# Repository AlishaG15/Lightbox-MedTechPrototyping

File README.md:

# Lightbox

A custom embedded systems project built for MedTech Prototyping (BME 254) at Duke University, Spring 2026 — a 3D-printed panda enclosure housing a hand-soldered PCB, Arduino Nano Every, and three independently controlled LEDs (two eyes and a nose).

---

## Overview

When a button is pressed, the panda's eyes light up for 5 seconds and its nose blinks for 10 seconds. The brightness of the eyes and blink rate of the nose are each controlled by a dedicated potentiometer mounted in the ears. An onboard heartbeat LED blinks at 1 Hz in all states to confirm the device is running.

---

## Hardware

| Component | Detail |
|---|---|
| Microcontroller | Arduino Nano Every (ATmega4809) |
| PCB | Custom single-sided board, hand-milled and soldered |
| LED drivers | IRFZ44 N-channel MOSFETs |
| Enclosure | 3D-printed PLA, two-part snap fit |
| Power | 9 V battery with SPST toggle switch |
| Controls | SPST push button + 2× 10 kΩ potentiometers |

---

## Firmware

Written in C++ using the Arduino framework via PlatformIO. Key design decisions:

- **State machine** with three explicit states: `IDLE`, `ANALOG_READ`, and `LED_OUTPUT`
- **Interrupt-driven** button input using `attachInterrupt()` — no polling in the main loop
- **Non-blocking timing** throughout using `millis()` — no `delay()` calls anywhere
- **PWM brightness control** on the eye LEDs via `analogWrite()`, mapped linearly from the potentiometer ADC reading
- **Clean digital blink** on the nose LED using `digitalWrite()` to avoid the Nano Every's 255/256 PWM artifact
- All pin assignments and timing constants defined as `#define` macros at the top of the file

```
IDLE ──(button press)──▶ ANALOG_READ ──▶ LED_OUTPUT ──(10 s elapsed)──▶ IDLE
```

---

## Testing Results

All measurements taken with a Tektronix TBS 1102B oscilloscope. Full analysis, with regression fits and 95% confidence intervals, is in the [technical report](testing/technical_report.ipynb) ([HTML version](testing/technical_report.html)); raw data is in [`testing/`](testing).

**Heartbeat LED**
- Period: 1000 ms, Frequency: 1.000 Hz, Duty cycle: 50.0%
- Identical in both IDLE and LED_OUTPUT states
- Zero measurable variation across 10 trials in each state (limited by oscilloscope resolution)

**Eye LED brightness (vs. potentiometer resistance)**
- Linear relationship (R² ≈ 1.0) from 0% duty cycle at max resistance to ~80% at minimum
- Did not reach 100% due to potentiometer mechanical travel limits

**Nose LED blink rate (vs. potentiometer resistance)**
- Linear relationship from 5.00 Hz (max resistance) to 7.45 Hz (min resistance)
- Lower bound matches spec exactly; upper bound limited by the same pot range constraint

---

## Gallery

| Assembled | Back panel |
|---|---|
|  |  |

| Internals (PCB) | Internals (Arduino + connectors) |
|---|---|
|  |  |

---

## Repository Layout

| Folder | Contents |
|---|---|
| [`src/`](src) | Firmware (`main.cpp`) |
| [`circuit/`](circuit) | KiCad schematic, PCB layout and MOSFET footprint |
| [`cad/`](cad) | Enclosure renders |
| [`testing/`](testing) | Oscilloscope data and technical report |
| [`images/`](images) | Photos of the assembled device |

---

## Built With

- **PlatformIO** — build system and upload toolchain
- **KiCad** — schematic capture and PCB layout
- **Fusion 360 / CAD** — enclosure design
- **Python / Jupyter** — data analysis and technical report (scipy, matplotlib, pandas)

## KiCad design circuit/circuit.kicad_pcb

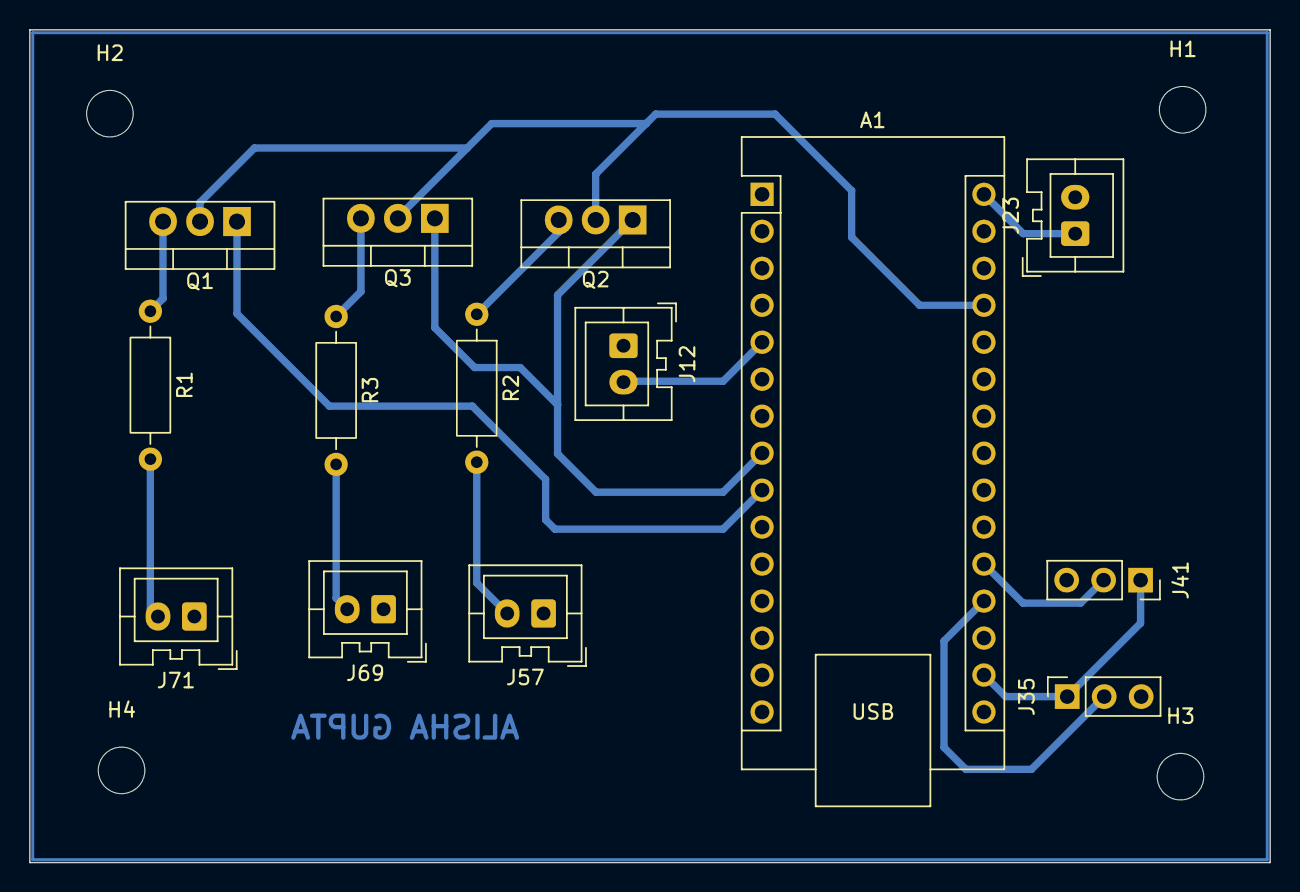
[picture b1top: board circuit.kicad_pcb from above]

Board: 2 copper layers, 85.2 x 57.2 mm, 18 parts (0 on the bottom side), 15 nets.

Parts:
A1: Arduino_Nano_Every; Arduino_Nano
H1, H2, H3, H4: MountingHole; MountingHole_3.2mm_M3
J12, J23: Conn_01x02_Pin; JST_XA_B02B-XASK-1_1x02_P2.50mm_Vertical
J35: POT_BRIGHT_CONN; PinSocket_1x03_P2.54mm_Vertical
J41: POT_BLINK_CONN; PinSocket_1x03_P2.54mm_Vertical
J57, J69, J71: B02B-XASK-1; JST_XA_B02B-XASK-1_1x02_P2.50mm_Vertical
Q1, Q2, Q3: IRFZ44N; TO-220-3_Vertical
R1, R2, R3: 1k; R_Axial_DIN0207_L6.3mm_D2.5mm_P10.16mm_Horizontal

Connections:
+3.3V: A1.17 (3V3), J35.1, J41.1
+5V: A1.27 (+5V), Q1.2, Q2.2, Q3.2
+9V: A1.30 (VIN), J23.1
BLINK_OUT: A1.9 (D6), Q1.1
BRIGHT_OUT: A1.8 (D5), Q2.1, Q3.1
BUTTON_IN: A1.5 (D2), J12.2
GND: A1.4 (GND), A1.29 (GND), J12.1, J23.2, J35.3, J41.3, J57.1, J69.1, J71.1
unnamed: J57.2, R2.2
unnamed: J69.2, R3.2
unnamed: J71.2, R1.2
unnamed: Q1.3, R1.1
unnamed: Q2.3, R2.1
unnamed: Q3.3, R3.1
POT_BLINK: A1.20 (A1), J41.2
POT_BRIGHT: A1.19 (A0), J35.2

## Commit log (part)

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2023-04-12 add resources
2023-04-12 Fix Nano Every chip and add Nane 33 Sense platform
2023-04-12 add button interrupt and blinking LED logic
2023-04-13 add tip about TTY permissions
2023-04-13 Add more functionality.
    * One-shot mode
    * Comments (including where timers should be used)
    * Sleep mode
2023-04-17 add comments about AVR-specific sleep library
2023-04-18 add analog voltage read hooks
2023-04-18 WIP: add KiCad ckt
2023-04-19 update schematic with components and notes
2023-04-19 ignore VS Code and KiCad local settings/backups
2023-04-19 update with schematic and firmware notes
2023-04-19 fix path to circuit schematic png
2023-04-19 add more hooks for functional code with outstanding TODO items
2023-04-20 Add digital writes for inv LED.
    * Add inv led writes opposite of non-inv led
    * Make sure off when device sleeps.
    * TECH DEBT - non-ideal sequential timing.
2023-04-20 implement amazing astable rate logic
2023-04-20 fix logic from Hz -> ms
2023-04-20 telling the TRUTH
2023-04-20 Revert "telling the TRUTH" (even though it is true)
    This reverts commit 87dc09f4477de0ba368f3c3d155b86e677ff7481.
2023-04-20 added "hi"
2023-04-20 change D10 -> D8
2023-04-21 Fix and complete code to work with both microcontrollers.
    * Comment out AVR-specific sleep library and associated code.
    * Add all monostable calculations.
    * Add INF and DBG logs.
    * Only read analog voltages at the start of the button press ON
    interval.
2023-04-26 FIX D8 -> D10; analog read float typecast
2023-04-26 add pinout to README
2023-04-26 fix rendering of pinout in markdown
2023-04-26 fix typo
2023-04-26 WIP: add content for duty cycle and TODOs
2023-04-27 refactor functions
2023-04-27 refactor into more functions
2023-04-27 refactor serial print statements
2023-04-27 Limit build configuration to just the Nano Every.
    Originally wanted to support the Nano Every and the Nano 33 BLE, but the
    33 is a PITA to use outside of Zephyr. AVR sleep library would need
    conditional compilation. Not worth it.
2023-04-27 UNTESTED: using millis timer and hook for variable duty cycle
2023-04-28 Implemented logic for millis-timer blink rate and duty cycle.
    TODO: Test with o-scope
2023-04-28 Fix timinig logic.
    * Remove serial print statements that were taking too long relative to
    the blink rate.
    * Avoid initial blink bias by not starting the timing based on the
    button press, but after the analog reads.
    * Correct next on/off time calculation logic.
2023-10-09 update README to reflect new project for F23
2023-10-09 remove spurious char
2023-10-09 add pinout and PlatformIO config for Arduino Nano
2023-10-09 add heartbeat LED spec
2023-10-18 update to include project management expectations
2023-10-20 add incremental lab tasks document
2023-10-20 add note about emulating button by connection to GND
2023-10-23 add analogRead doc link
2024-03-18 limit board configs to Arduino Nano Every
2024-03-18 update project for S24, including testing section and explicit state machine framework
2024-03-18 add 'What to Submit' section
2024-03-18 rm LabTasks doc
2024-03-18 add threaded inserts resource
2024-03-19 add proposed timeline
2024-03-26 add PWM hyperlinks
2024-03-30 add note about adding name to copper pour
2024-03-30 add checklist of commonly missed things
2024-03-30 add resistor footprint example
2024-03-30 adjust size of the resistor footprint image
2024-04-21 add note on pics/video to submit
2024-10-15 update for F24
2024-10-15 change title of project
2024-10-15 add technical report template
2024-10-15 rm unused files / directories
2024-10-15 add example enclosures
2024-10-15 add latest Jupyter NB template
2024-10-15 add grading criteria
2024-10-15 add sleep library
2024-10-16 fix markdown
2024-11-04 add DRU
2024-11-04 add ERC/DRC CI script
2024-11-04 add updated technical report with some examples
2024-11-04 update tech report example to include linear fit w/ 95% CI
2024-11-08 ignore KiCad *.lck files
2025-03-25 Add IRFZ44 KiCad symbol and footprint.
    `sym-lib-table` allows the part to be seen in the project-specific library
    Closes #6
2025-03-25 Update KiCad template project.
    * Remove confusing pseudo-connections and test points.
    * Add heirarchecal sheets for different sub-circuits.
    * Add placeholder metadata in the schematic.
    * Add pinout for the Arduino Nano Every.
    Closes #5
2025-03-25 Update handout for S25.
    * Remove confusing mock circuit schematic.
    * Update code boilerplate to match handout better.
    * Get rid of unused `go_to_sleep()` function and the associated library include.
    * Add extra note about valid PWM pins.
    * Update what the submit (Gitlab and Gradescope components)
    * Remove requirement to present device.
2025-03-25 Add requirement to drive each LED with IRFZ44 MOSFET.
    Issue #6
2025-03-25 Updates to handout for S25.
    * Move images to an images/ dir.
    * Add connector interference image.
    * Convert to using HTML image rendering to control image width.
    * Ignore KiCad cache file and DS_Store
    * Add starter parts in KiCad schematic.
    * Update URL hyperlink formatting.
2025-03-25 add example connectors to use in schematic
2025-03-25 remove unnecessary hex data extraction sections
2025-03-25 add more sections for report to match the handout
2025-03-27 update grading criteria for lightbox project
2025-03-27 update analysis ask for heartbeat LED
2025-04-05 do not error exit on violations; cat RC reports
2025-04-07 Update footprints and values.
    * Convert the `IRFZ44N` to use a generic TO-220 vertical footprint since
    the custom footprint isn't importing correctly.
    * Update the footprints for the socket connectors and the resistors.
    * Exclude some components from the board.
    * Add some nominal part values (e.g., battery).
2026-02-04 consolidate schematic to single root page
2026-02-04 rm unused hexdump data file
2026-02-04 Add Python environment and requirements files for technical report notebook
2026-02-04 Add clearance around PinHeader footprint.
    The default footprint for the 1x2 pin header was too small, leading to
    connectors physically conflicting with one another on the PCB.
    This adds 125 mil of clearance to the DRU for this footprint, based on
    the B02B-XASK-1 2-pin connector that we are using.
2026-02-04 add more clearance around holes
2026-02-04 update footprint for pin socket to B02B-XASK-1
2026-02-04 Remove unnecessary clearance rule around 1x2 connector.
    1. This didn't work as intended.
    2. The actual B02B-XASK-1 connector footprint is available to use!
2026-02-04 rm pic of connector interference now that correct footprint is being used
2026-02-04 rm resistor footprint image (proper footpring used in KiCad)
2026-02-04 add more notes about excluding things from board and connectors
2026-02-04 update markdown syntax and fix typos
2026-02-04 make headings larger
2026-02-04 change order of section for more logical flow
2026-02-16 update code template
2026-02-16 update how stuff is submitted
2026-02-16 ignore local __pycache__/
2026-02-24 connected battery to switch via pins
2026-02-24 added all components via pins or on-board
2026-02-26 add 3-pin connector and jumper
2026-03-05 updated footprints, pcb components, mounting holes, and edge cuts
2026-03-16 made changes to lightbox pcb - fix mistakes from KiCad Review Issue
2026-03-16 deleted red filled zone
2026-03-17 update DRU for more F/B part/Cu check and better clearances
2026-03-18 Fixed B. Cu layer and moved parts to correct layer (revision number v1.1.1)
2026-03-18 updated name to GND
2026-03-18 moved mounting holes
2026-03-29 Revert "moved mounting holes"
    This reverts commit 6c6eda3e60cd54308894f1d0f9ce76ea73f12124.
2026-03-29 added second version of pcb smaller and more compact
2026-03-29 updated folder directory and added v2 of pcb
2026-04-01 uploaded pcb with metadata
2026-04-01 Revert "uploaded pcb with metadata"
    This reverts commit 118884daa18b4dd73780fb005e8cf3b07a4ea623.
2026-04-01 pushing v2 out again deleted lightboxV1 and lightboxV2 folders
2026-04-11 updated firmware for review
2026-04-11 deleted main2.cpp
2026-04-27 finished testing, technical report, and images
2026-04-28 udpated readme
2026-04-28 Remove image and update README formatting
    Removed image from README and adjusted formatting.
